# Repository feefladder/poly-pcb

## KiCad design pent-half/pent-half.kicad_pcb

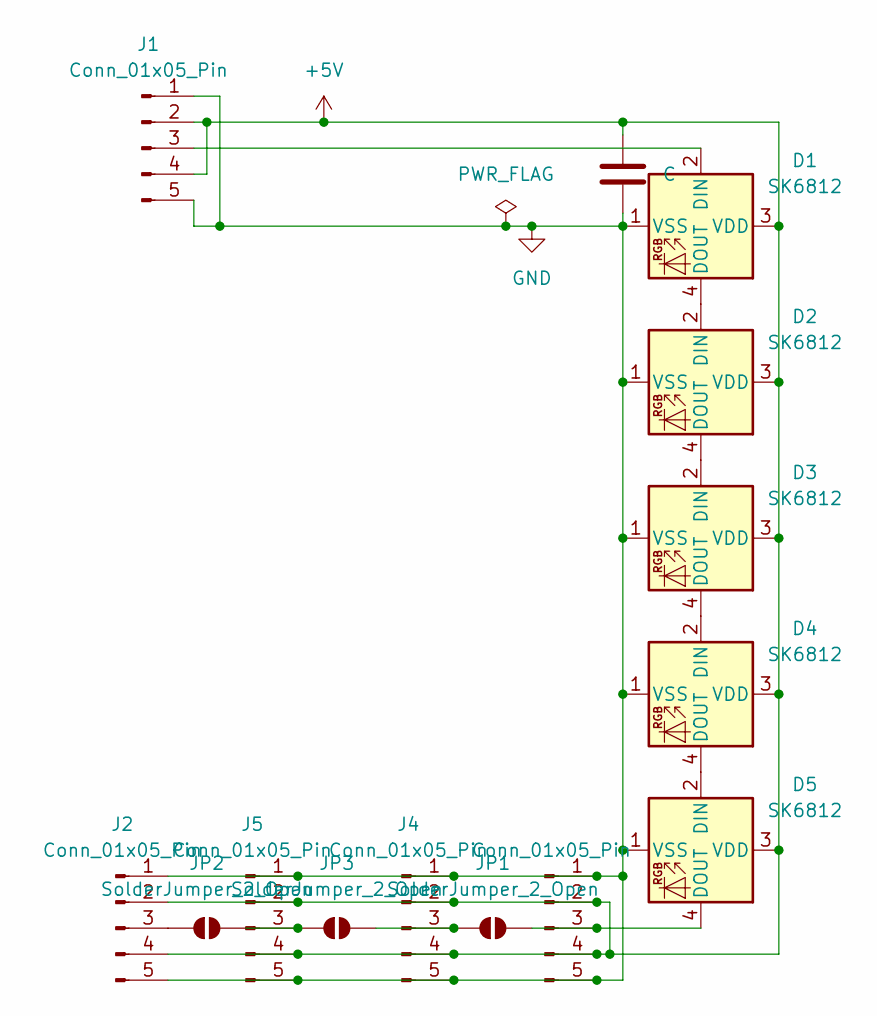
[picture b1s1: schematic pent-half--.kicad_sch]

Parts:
C1: C; C_0805_2012Metric_Pad1.18x1.45mm_HandSolder
D1, D2, D3, D4, D5: SK6812; LED_SK6812_PLCC4_5.0x5.0mm_P3.2mm
J1, J2, J3, J4, J5: Conn_01x05_Pin; PinHeader_1x05_P2.54mm_Vertical
JP1, JP2, JP3: SolderJumper_2_Open; SolderJumper-2_P1.3mm_Open_Pad1.0x1.5mm

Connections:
+5V: C1.2, D1.3 (VDD), D2.3 (VDD), D3.3 (VDD), D4.3 (VDD), D5.3 (VDD), J1.2, J1.4, J2.2, J2.4, J3.2, J3.4, J4.2, J4.4, J5.2, J5.4
GND: C1.1, D1.1 (VSS), D2.1 (VSS), D3.1 (VSS), D4.1 (VSS), D5.1 (VSS), J1.1, J1.5, J2.1, J2.5, J3.1, J3.5, J4.1, J4.5, J5.1, J5.5
unnamed: D1.2 (DIN), J1.3
unnamed: D1.4 (DOUT), D2.2 (DIN)
unnamed: D2.4 (DOUT), D3.2 (DIN)
unnamed: D3.4 (DOUT), D4.2 (DIN)
unnamed: D4.4 (DOUT), D5.2 (DIN)
unnamed: D5.4 (DOUT), J3.3, JP1.2 (B)
unnamed: J2.3, JP2.1 (A)
unnamed: J4.3, JP1.1 (A), JP3.2 (B)
unnamed: J5.3, JP2.2 (B), JP3.1 (A)

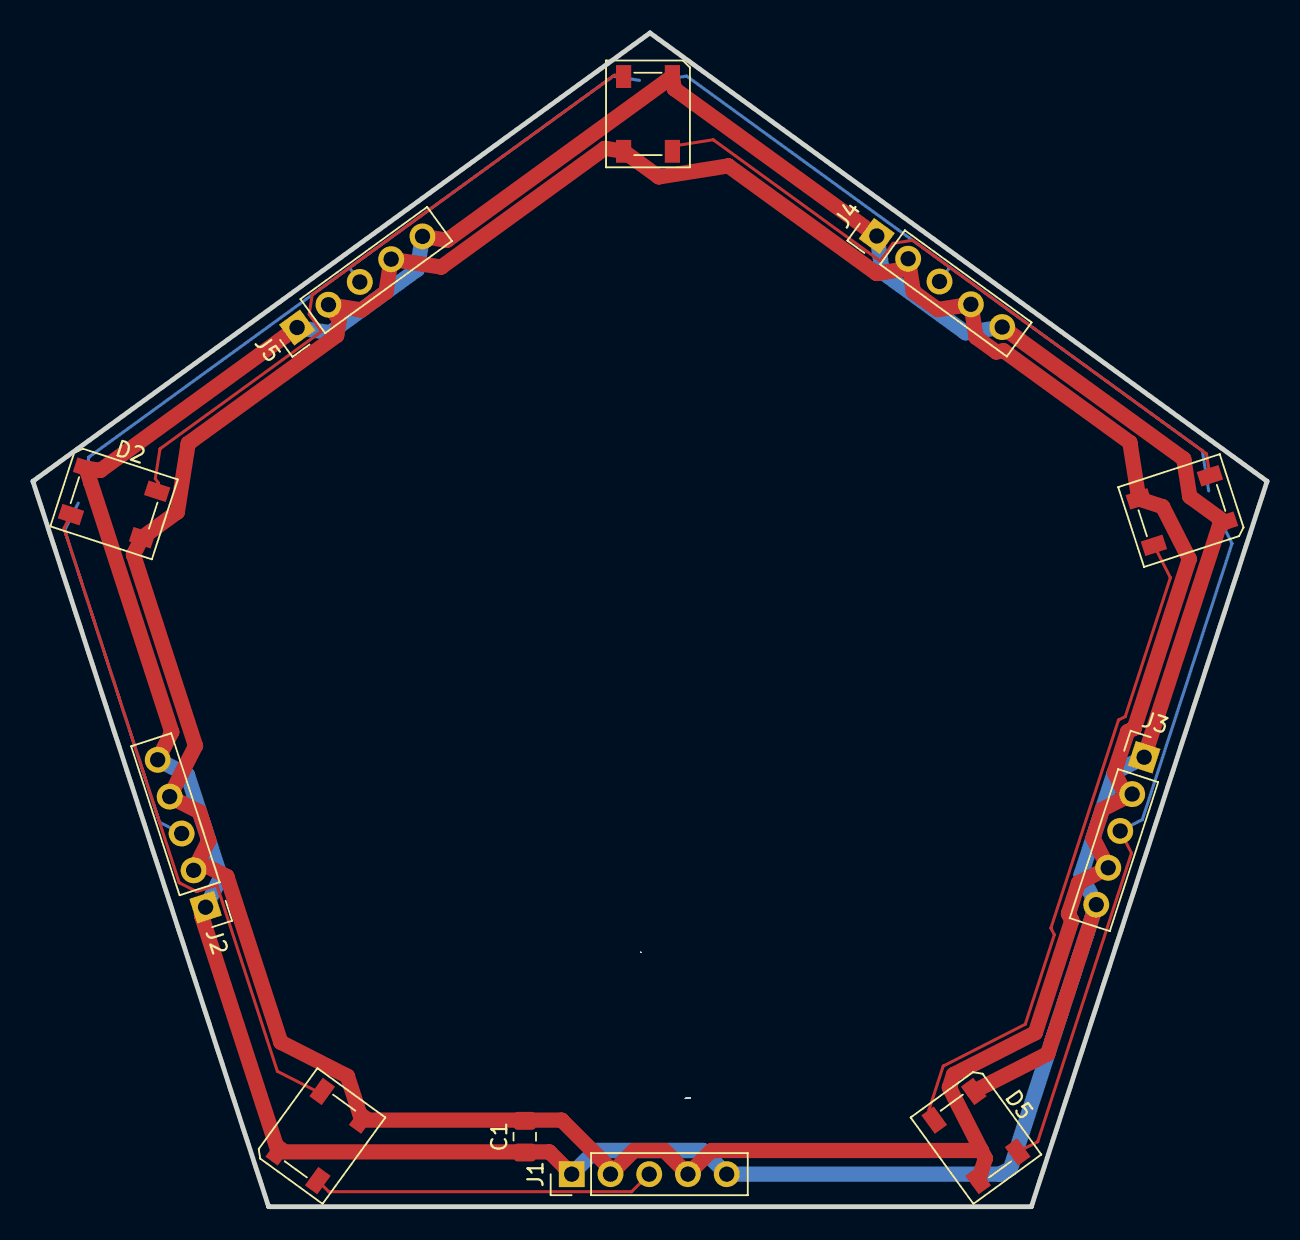
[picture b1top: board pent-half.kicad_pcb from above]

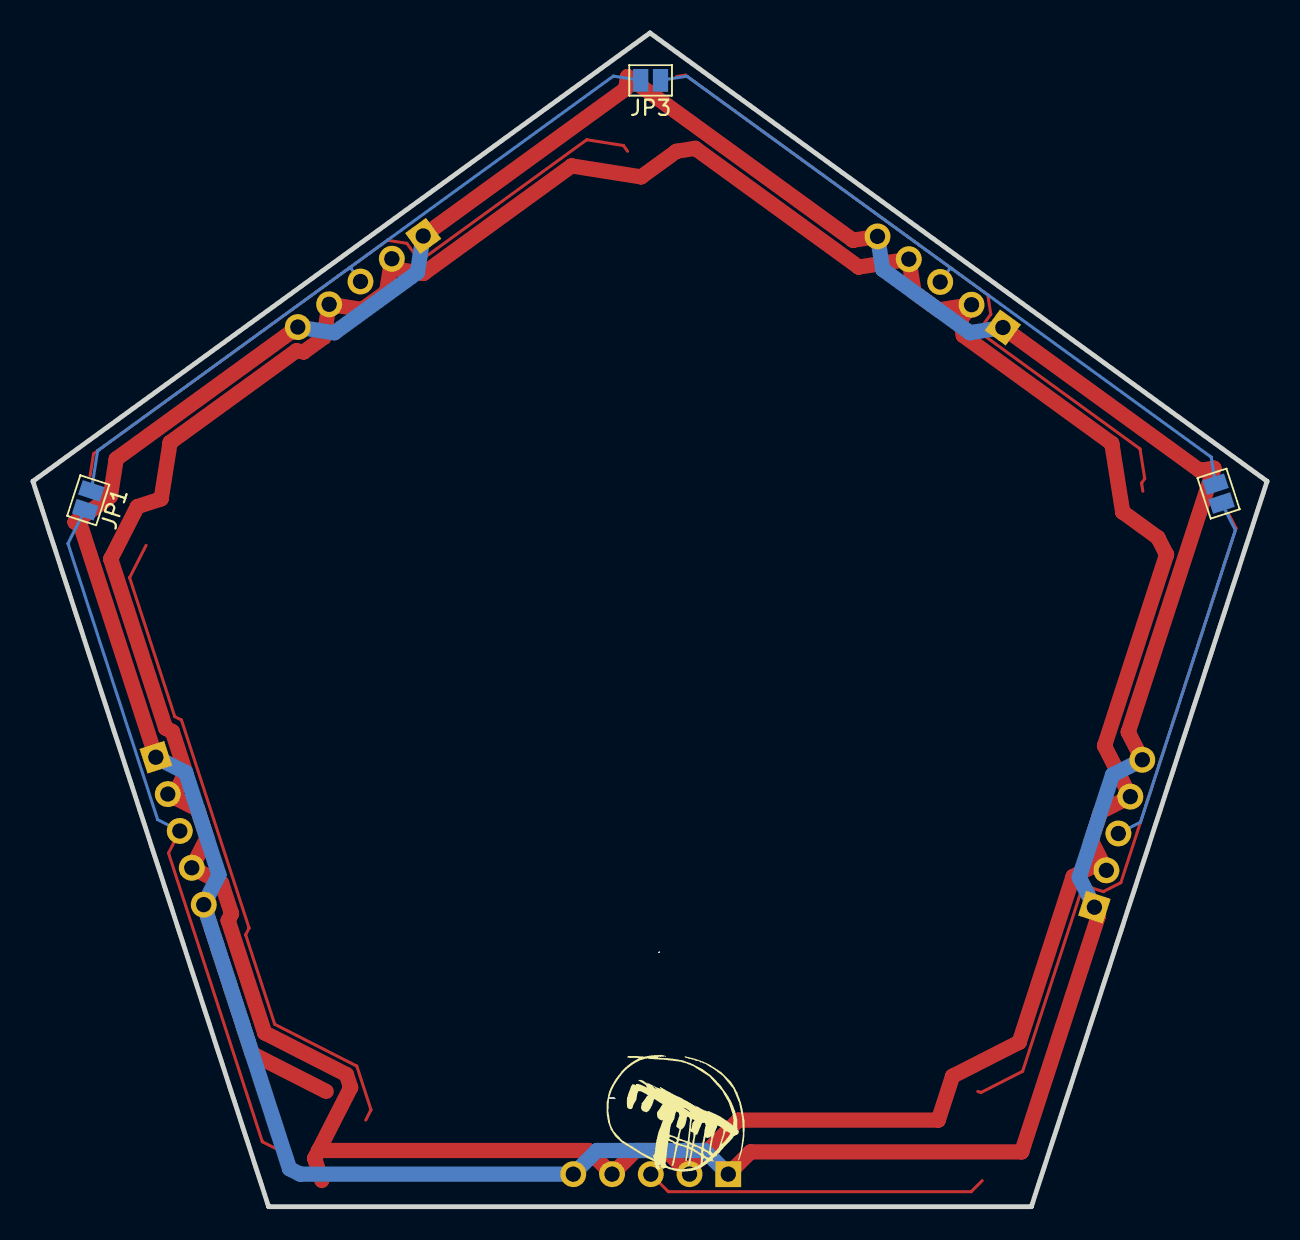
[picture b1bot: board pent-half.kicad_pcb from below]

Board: 2 copper layers, 80.9 x 76.9 mm, 14 parts (3 on the bottom side), 11 nets.

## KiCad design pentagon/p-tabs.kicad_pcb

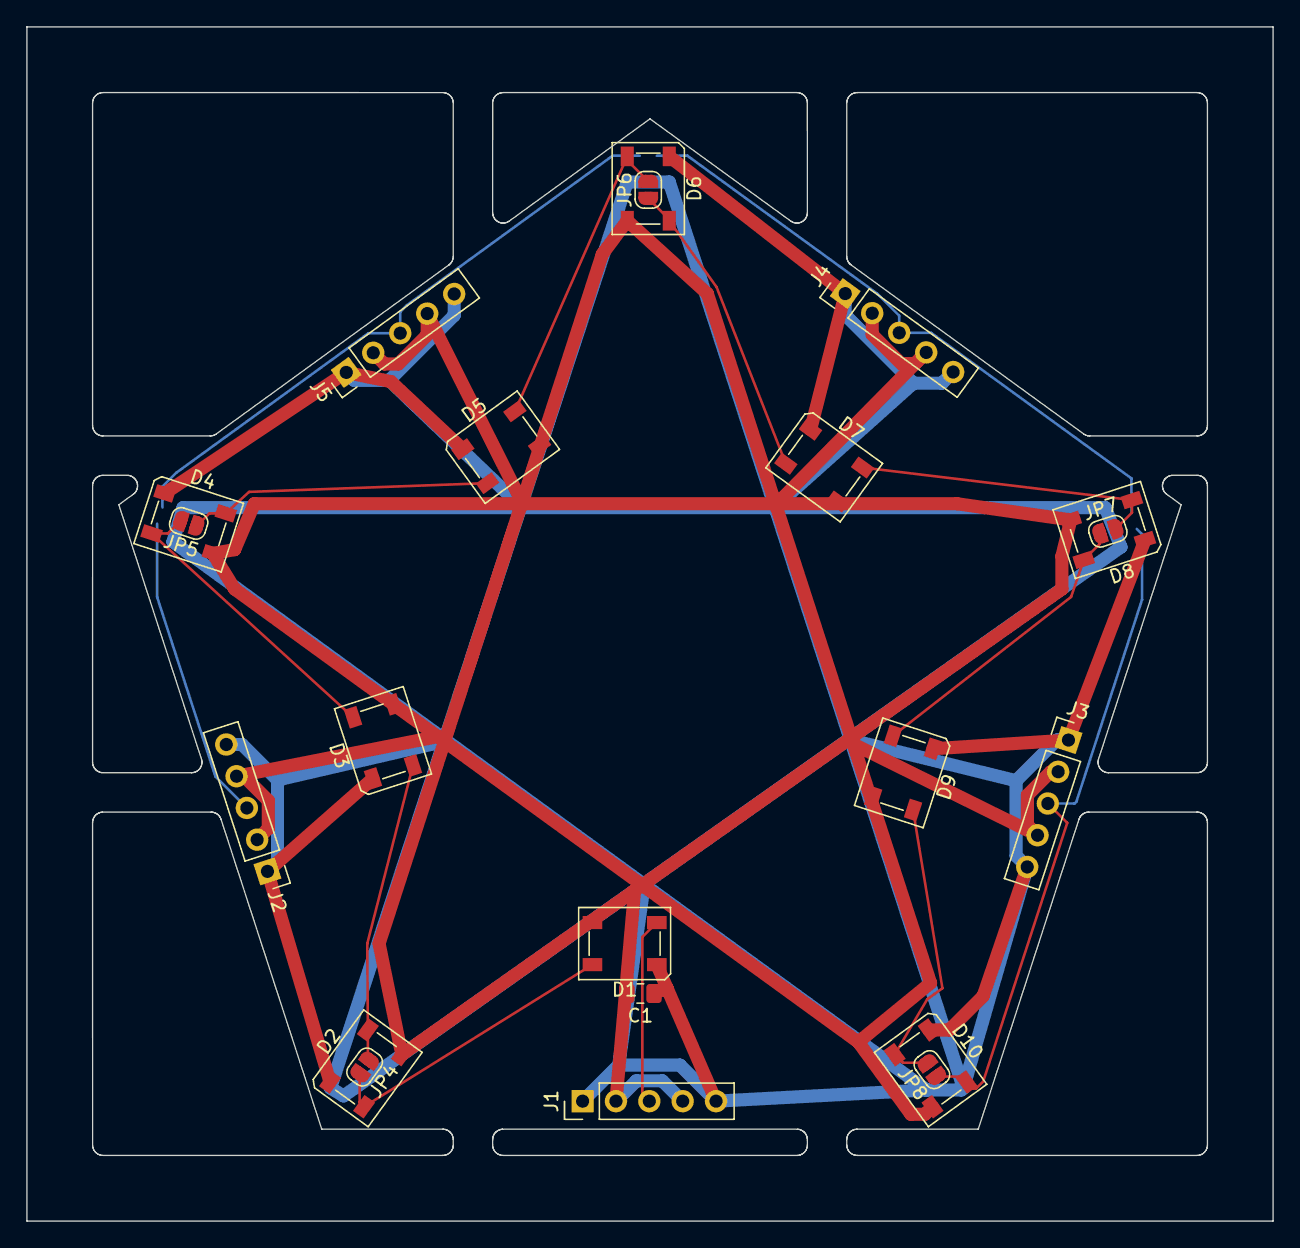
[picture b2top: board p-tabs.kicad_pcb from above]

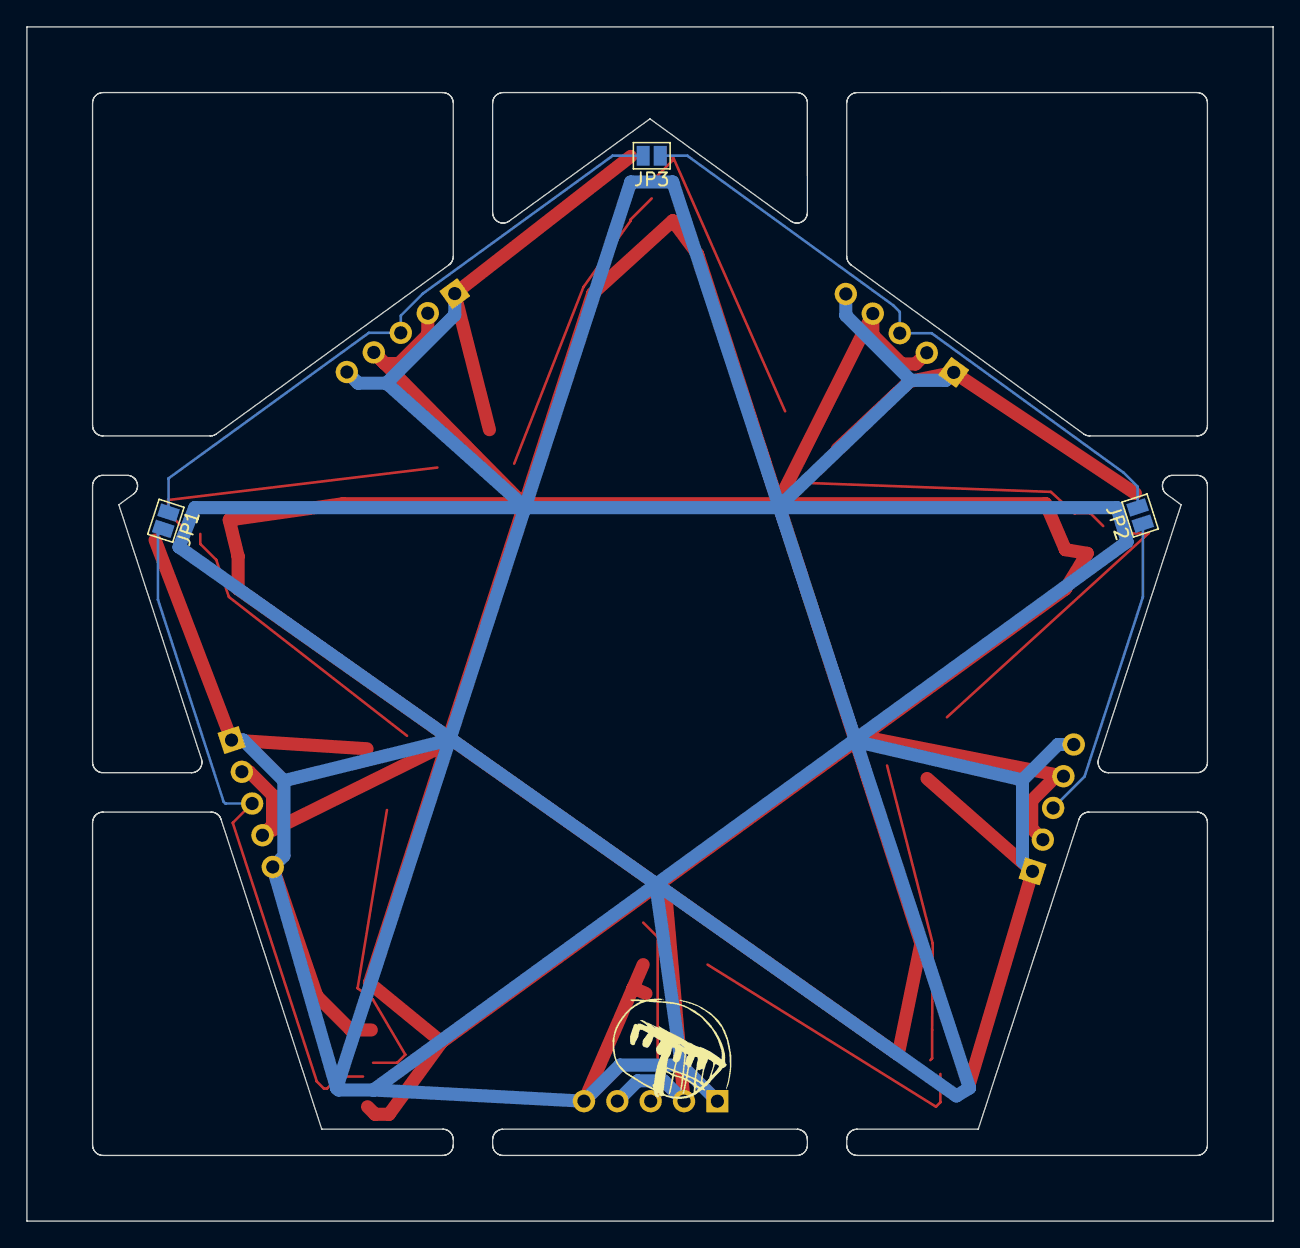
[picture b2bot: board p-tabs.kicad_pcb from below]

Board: 2 copper layers, 94.9 x 90.9 mm, 24 parts (3 on the bottom side), 16 nets.

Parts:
C1: C; C_0805_2012Metric_Pad1.18x1.45mm_HandSolder
D1, D2, D3, D4, D5, D6, D7, D8, D9, D10: SK6812; LED_SK6812_PLCC4_5.0x5.0mm_P3.2mm
J1, J2, J3, J4, J5: Conn_01x05_Pin; PinHeader_1x05_P2.54mm_Vertical
JP1, JP2, JP3: SolderJumper_2_Open; SolderJumper-2_P1.3mm_Open_Pad1.0x1.5mm
JP4, JP5, JP6, JP7, JP8: SolderJumper_2_Open; SolderJumper-2_P1.3mm_Open_RoundedPad1.0x1.5mm

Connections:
Board_0-+5V: C1.2, D1.3 (VDD), D2.3 (VDD), D3.3 (VDD), D4.3 (VDD), D5.3 (VDD), D6.3 (VDD), D7.3 (VDD), D8.3 (VDD), D9.3 (VDD), D10.3 (VDD), J1.2, J1.4, J2.2, J2.4, J3.2, J3.4, J4.2, J4.4, J5.2, J5.4
Board_0-GND: C1.1, D1.1 (VSS), D2.1 (VSS), D3.1 (VSS), D4.1 (VSS), D5.1 (VSS), D6.1 (VSS), D7.1 (VSS), D8.1 (VSS), D9.1 (VSS), D10.1 (VSS), J1.1, J1.5, J2.1, J2.5, J3.1, J3.5, J4.1, J4.5, J5.1, J5.5
Board_0-Net-(D1-DIN): D1.2 (DIN), J1.3
Board_0-Net-(D1-DOUT): D1.4 (DOUT), D2.2 (DIN), JP4.2 (B)
Board_0-Net-(D2-DOUT): D2.4 (DOUT), D3.2 (DIN), JP4.1 (A)
Board_0-Net-(D3-DOUT): D3.4 (DOUT), D4.2 (DIN), JP5.2 (B)
Board_0-Net-(D4-DOUT): D4.4 (DOUT), D5.2 (DIN), JP5.1 (A)
Board_0-Net-(D5-DOUT): D5.4 (DOUT), D6.2 (DIN), JP6.2 (B)
Board_0-Net-(D6-DOUT): D6.4 (DOUT), D7.2 (DIN), JP6.1 (A)
Board_0-Net-(D7-DOUT): D7.4 (DOUT), D8.2 (DIN), JP7.2 (B)
Board_0-Net-(D8-DOUT): D8.4 (DOUT), D9.2 (DIN), JP7.1 (A)
Board_0-Net-(D10-DIN): D9.4 (DOUT), D10.2 (DIN), JP8.2 (B)
Board_0-Net-(D10-DOUT): D10.4 (DOUT), J3.3, JP1.2 (B), JP8.1 (A)
Board_0-Net-(J2-Pin_3): J2.3, JP2.1 (A)
Board_0-Net-(J4-Pin_3): J4.3, JP1.1 (A), JP3.2 (B)
Board_0-Net-(J5-Pin_3): J5.3, JP2.2 (B), JP3.1 (A)
